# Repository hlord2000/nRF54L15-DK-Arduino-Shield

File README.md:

# nRF54L15-DK to Arduino Shield Adapter

This adapter board allows you to connect Arduino shields to your nRF54L15-DK development kit for basic prototyping needs.

<div align="center">
  
</div>

## Features

- Compatible with nRF54L15-DK development kit
- Standard Arduino shield form factor
- Solder jumpers for pin configuration flexibility

## ⚠️ Important Usage Notes

- **3.3V OPERATION ONLY** - Configure your nRF54L15-DK to use +3.3V logic
- Pins with solder jumpers are **NOT CONNECTED BY DEFAULT**
- **PINS WITH SOLDER JUMPERS MUST BE RECONFIGURED WITH THE BOARD CONFIGURATOR APP TO BE USED**

<div align="center">
  
</div>

## Getting Started

1. Ensure your nRF54L15-DK is configured for 3.3V operation
2. Attach this adapter board to your nRF54L15-DK
3. For pins with solder jumpers:
   - Keep jumpers open for default configuration
   - If needed, close jumpers and reconfigure pins using the Board Configurator App

## Compatibility

This adapter is designed for basic Arduino shields that operate at 3.3V logic levels. Shields requiring 5V logic are not supported without additional level shifting.

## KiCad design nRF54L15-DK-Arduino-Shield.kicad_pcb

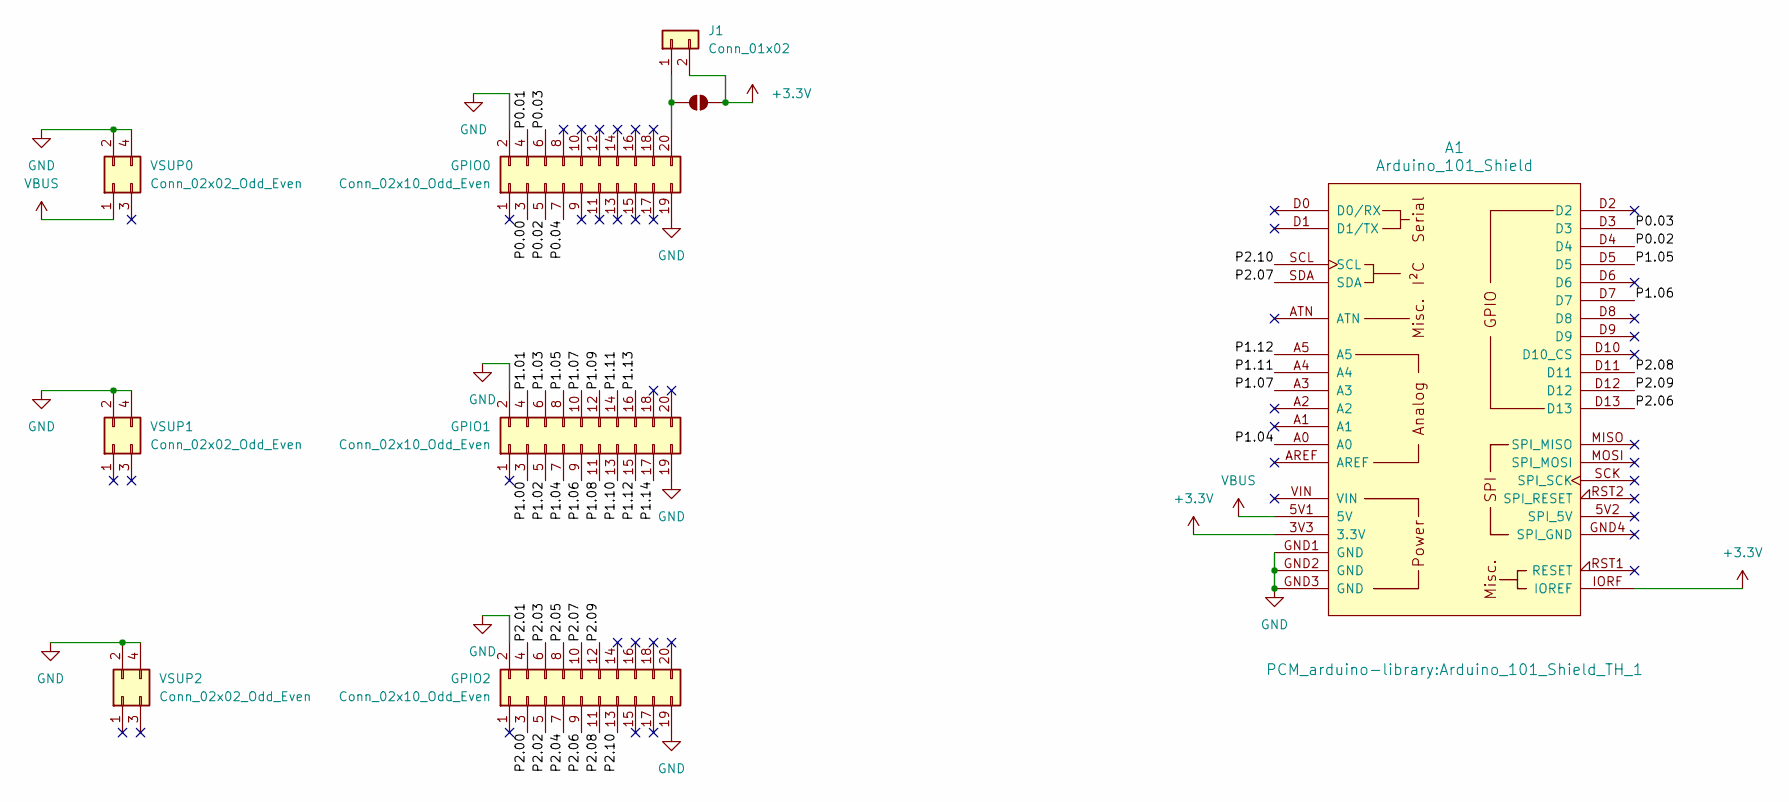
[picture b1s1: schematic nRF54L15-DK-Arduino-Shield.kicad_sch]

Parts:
A1: Arduino_101_Shield; Arduino_101_Shield_TH_1
GPIO0, GPIO1, GPIO2: Conn_02x10_Odd_Even; PinSocket_2x10_P2.54mm_Vertical
J1: Conn_01x02; PinHeader_1x02_P2.54mm_Vertical
JP1: SolderJumper_2_Open; SolderJumper-2_P1.3mm_Open_RoundedPad1.0x1.5mm
VSUP0, VSUP1, VSUP2: Conn_02x02_Odd_Even; PinSocket_2x02_P2.54mm_Vertical

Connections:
+3.3V: A1.3V3 (3.3V), A1.IORF (IOREF), J1.2, JP1.2 (B)
/P0.00: GPIO0.3
/P0.01: GPIO0.4
/P0.02: A1.D4, GPIO0.5
/P0.03: A1.D3, GPIO0.6
/P0.04: GPIO0.7
/P1.00: GPIO1.3
/P1.01: GPIO1.4
/P1.02: GPIO1.5
/P1.03: GPIO1.6
/P1.04: A1.A0, GPIO1.7
/P1.05: A1.D5, GPIO1.8
/P1.06: A1.D7, GPIO1.9
/P1.07: A1.A3, GPIO1.10
/P1.08: GPIO1.11
/P1.09: GPIO1.12
/P1.10: GPIO1.13
/P1.11: A1.A4, GPIO1.14
/P1.12: A1.A5, GPIO1.15
/P1.13: GPIO1.16
/P1.14: GPIO1.17
/P2.00: GPIO2.3
/P2.01: GPIO2.4
/P2.02: GPIO2.5
/P2.03: GPIO2.6
/P2.04: GPIO2.7
/P2.05: GPIO2.8
/P2.06: A1.D13, GPIO2.9
/P2.07: A1.SDA, GPIO2.10
/P2.08: A1.D11, GPIO2.11
/P2.09: A1.D12, GPIO2.12
/P2.10: A1.SCL, GPIO2.13
GND: A1.GND1 (GND), A1.GND2 (GND), A1.GND3 (GND), GPIO0.2, GPIO0.19, GPIO1.2, GPIO1.19, GPIO2.2, GPIO2.19, VSUP0.2, VSUP0.4, VSUP1.2, VSUP1.4, VSUP2.2, VSUP2.4
unnamed: GPIO0.20, J1.1, JP1.1 (A)
VBUS: A1.5V1 (5V), VSUP0.1

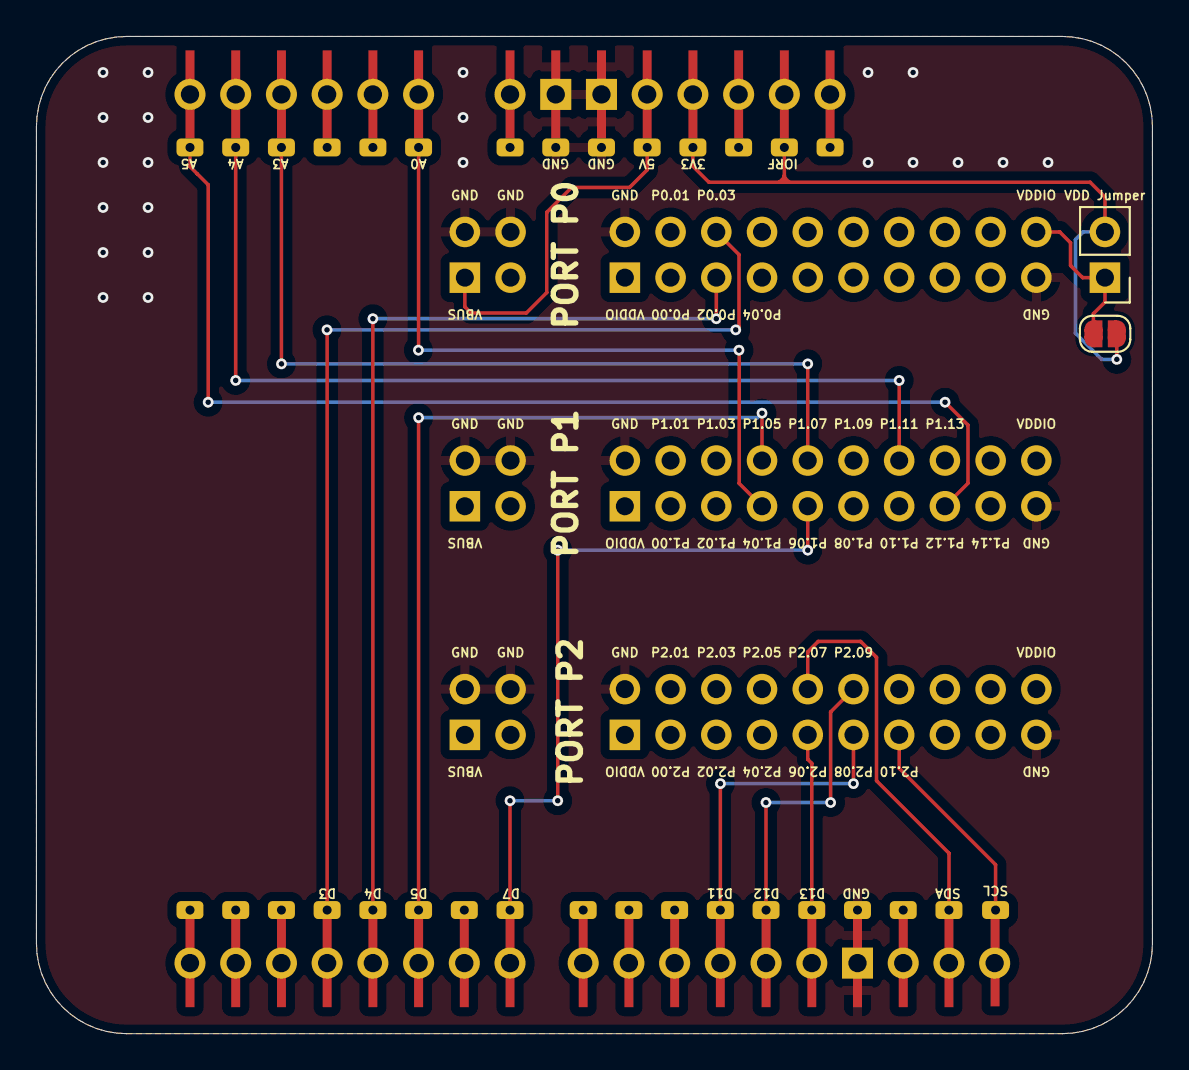
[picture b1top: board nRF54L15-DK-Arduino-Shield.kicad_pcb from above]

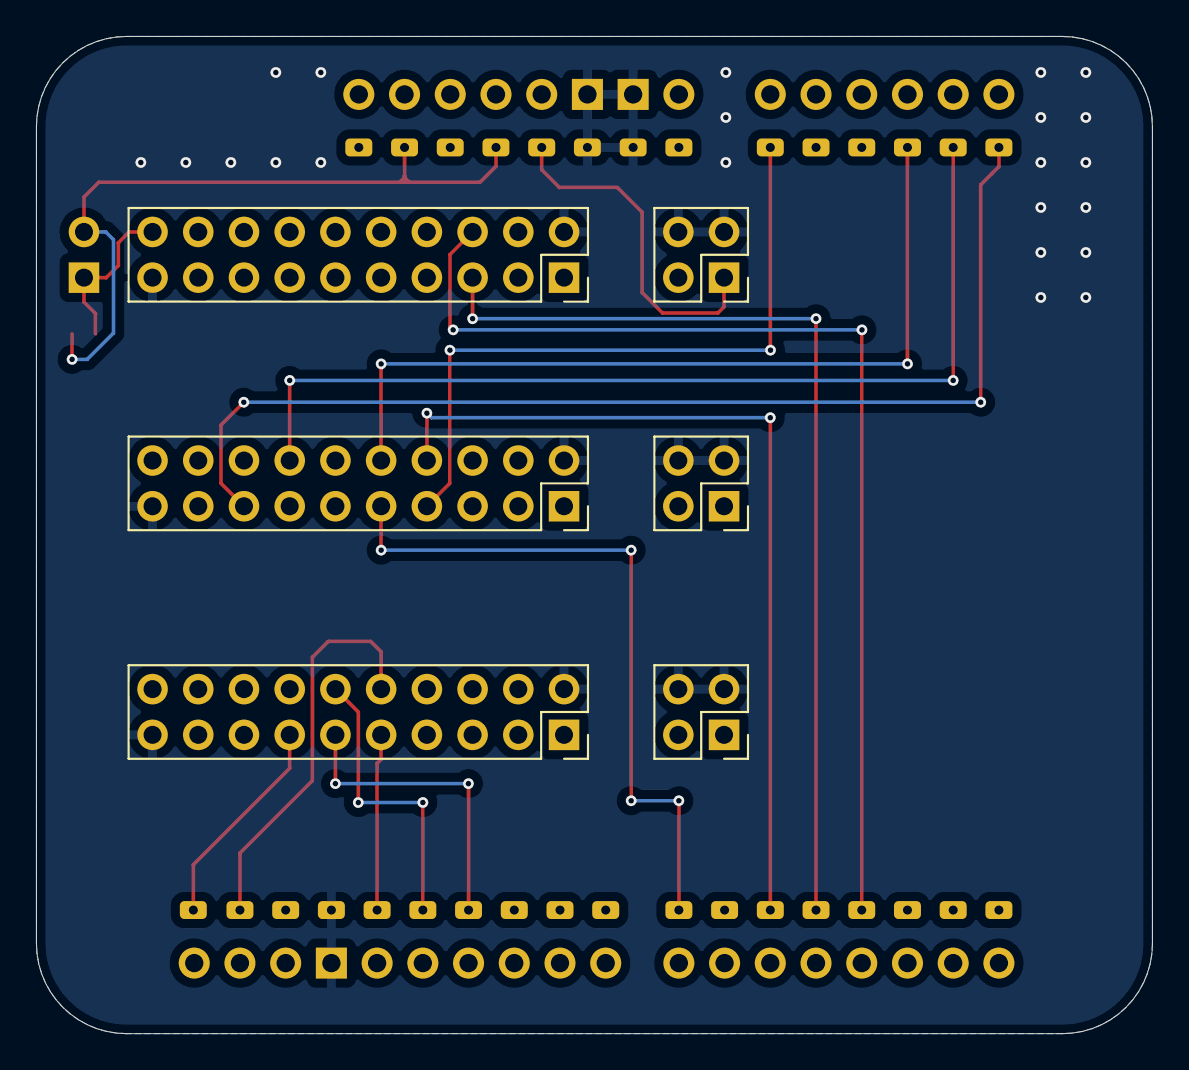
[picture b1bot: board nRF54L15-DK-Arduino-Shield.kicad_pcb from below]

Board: 2 copper layers, 62.0 x 55.4 mm, 9 parts (6 on the bottom side), 17 nets.

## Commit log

2025-03-03 Initial commit.
2025-03-21 Updates for LR1110 Arduino shield
2025-06-19 Added VDD jumper
